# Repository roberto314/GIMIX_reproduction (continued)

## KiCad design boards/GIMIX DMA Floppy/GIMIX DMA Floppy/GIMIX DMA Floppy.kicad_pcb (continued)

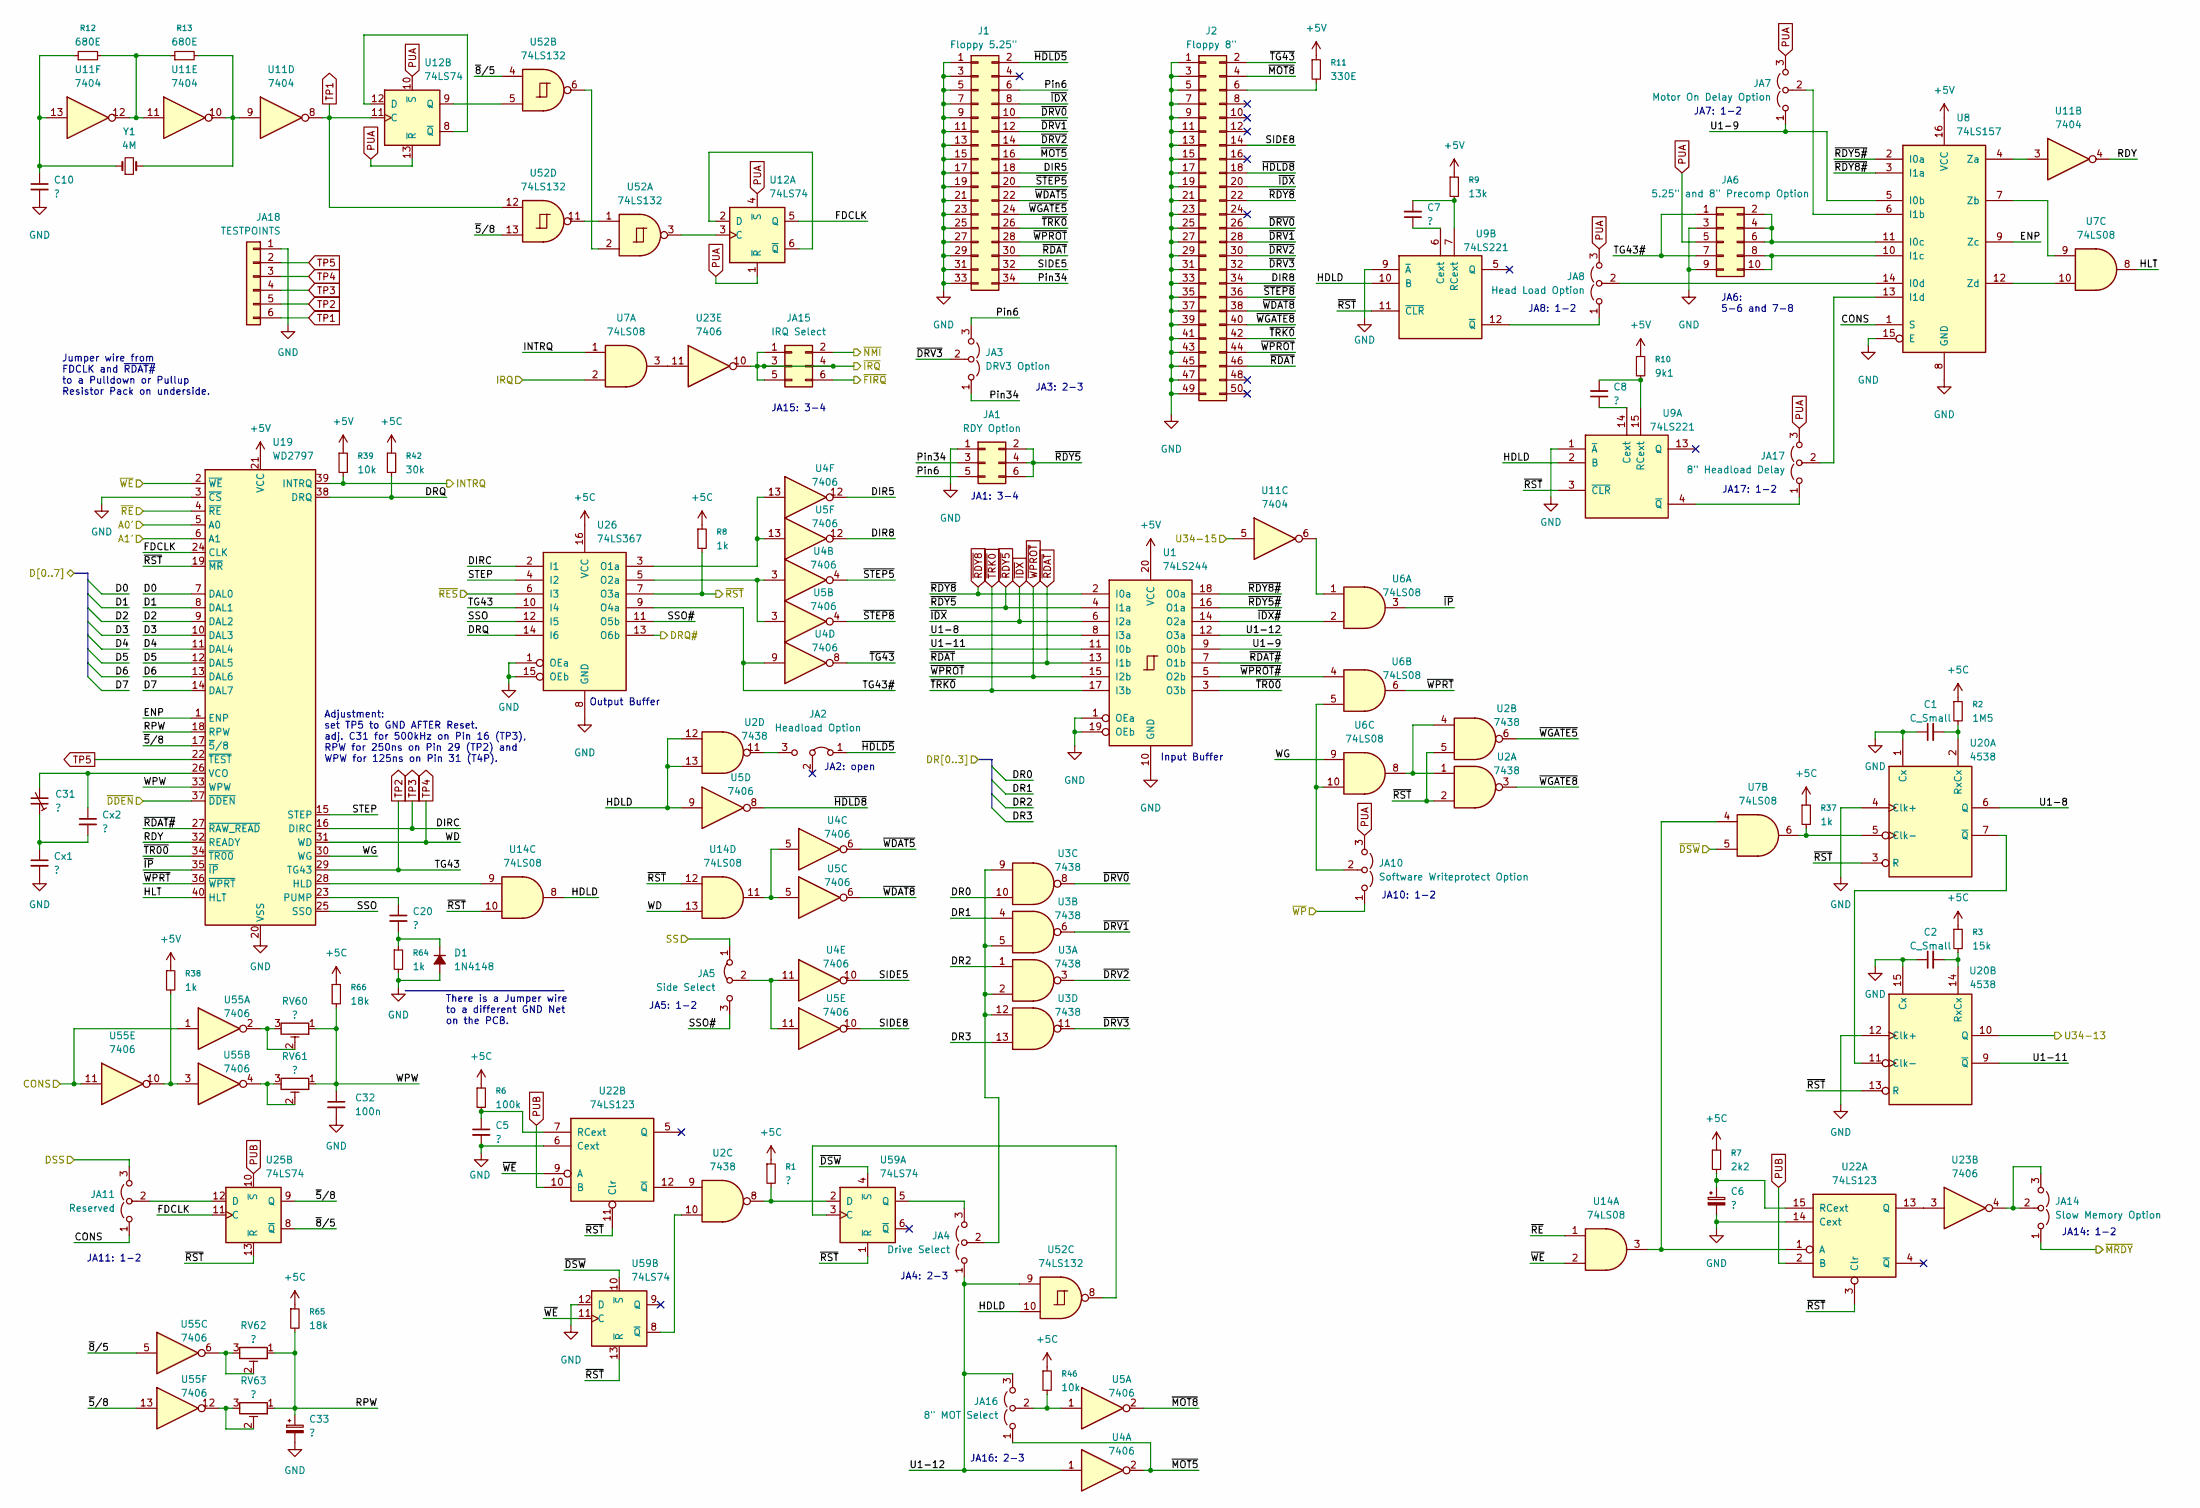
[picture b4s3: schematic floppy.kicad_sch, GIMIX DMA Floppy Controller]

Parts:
C1, C2: C_Small; C_Disc_D3.0mm_W1.6mm_P2.50mm
C5, C7, C8, C33: ?; C_Disc_D3.0mm_W1.6mm_P2.50mm
C6, C10: ?; C_Disc_D4.7mm_W2.5mm_P5.00mm
C20: ?; C_Rect_L11.0mm_W5.1mm_P10.00mm_MKT
C31: ?; Capacitor_Trim
C32: 100n; C_Disc_D3.0mm_W1.6mm_P2.50mm
Cx1, Cx2: ?; C_1206_3216Metric_Pad1.33x1.80mm_HandSolder
D1: 1N4148; D_A-405_P10.16mm_Horizontal
J1: Floppy 5.25"; PinHeader_2x17_P2.54mm_Vertical
J2: Floppy 8"; PinHeader_2x25_P2.54mm_Vertical
JA1: RDY Option; PinHeader_2x03_P2.54mm_Vertical
JA2: Headload Option; PinHeader_1x03_P2.54mm_Vertical
JA3: DRV3 Option; PinHeader_1x03_P2.54mm_Vertical
JA4: Drive Select; PinHeader_1x03_P2.54mm_Vertical
JA5: Side Select; PinHeader_1x03_P2.54mm_Vertical
JA6: 5.25" and 8" Precomp Option; PinHeader_2x05_P2.54mm_Vertical
JA7: Motor On Delay Option; PinHeader_1x03_P2.54mm_Vertical
JA8: Head Load Option; PinHeader_1x03_P2.54mm_Vertical
JA10: Software Writeprotect Option; PinHeader_1x03_P2.54mm_Vertical
JA11: Reserved; PinHeader_1x03_P2.54mm_Vertical
JA14: Slow Memory Option; PinHeader_1x03_P2.54mm_Vertical
JA15: IRQ Select; PinHeader_2x03_P2.54mm_Vertical
JA16: 8" MOT Select; PinHeader_1x03_P2.54mm_Vertical
JA17: 8" Headload Delay; PinHeader_1x03_P2.54mm_Vertical
JA18: TESTPOINTS; PinHeader_1x06_P2.54mm_Vertical
R1: ?; R_Axial_DIN0207_L6.3mm_D2.5mm_P10.16mm_Horizontal
R2: 1M5; R_Axial_DIN0207_L6.3mm_D2.5mm_P10.16mm_Horizontal
R3: 15k; R_Axial_DIN0207_L6.3mm_D2.5mm_P10.16mm_Horizontal
R6: 100k; R_Axial_DIN0207_L6.3mm_D2.5mm_P10.16mm_Horizontal
R7: 2k2; R_Axial_DIN0207_L6.3mm_D2.5mm_P10.16mm_Horizontal
R8, R37, R38, R64: 1k; R_Axial_DIN0207_L6.3mm_D2.5mm_P10.16mm_Horizontal
R9: 13k; R_Axial_DIN0207_L6.3mm_D2.5mm_P10.16mm_Horizontal
R10: 9k1; R_Axial_DIN0207_L6.3mm_D2.5mm_P10.16mm_Horizontal
R11: 330E; R_Axial_DIN0207_L6.3mm_D2.5mm_P10.16mm_Horizontal
R12, R13: 680E; R_Axial_DIN0207_L6.3mm_D2.5mm_P10.16mm_Horizontal
R39, R46: 10k; R_Axial_DIN0207_L6.3mm_D2.5mm_P10.16mm_Horizontal
R42: 30k; R_Axial_DIN0207_L6.3mm_D2.5mm_P10.16mm_Horizontal
R65, R66: 18k; R_Axial_DIN0207_L6.3mm_D2.5mm_P10.16mm_Horizontal
RV60, RV61, RV62, RV63: ?; Potentiometer_Bourns_3005_Horizontal
U1: 74LS244; DIP-20_W7.62mm
U2, U3: 7438; DIP-14_W7.62mm
U4, U5, U23, U55: 7406; DIP-14_W7.62mm
U6, U7, U14: 74LS08; DIP-14_W7.62mm
U8: 74LS157; DIP-16_W7.62mm
U9: 74LS221; DIP-16_W7.62mm
U11: 7404; DIP-14_W7.62mm
U12, U25, U59: 74LS74; DIP-14_W7.62mm
U19: WD2797; DIP-40_W15.24mm
U20: 4538; DIP-16_W7.62mm
U22: 74LS123; DIP-16_W7.62mm
U26: 74LS367; DIP-16_W7.62mm
U52: 74LS132; DIP-14_W7.62mm
Y1: 4M; Crystal_HC49-U_Vertical

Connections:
+5C: R1.1, R2.1, R3.1, R6.1, R7.1, R8.1, R37.1, R42.1, R46.1, R65.1, R66.1, U26.16 (VCC); also elsewhere on the board
+5V: R9.1, R10.1, R11.1, R38.1, R39.1, U1.20 (VCC), U8.16 (VCC), U19.21 (VCC); also elsewhere on the board
/A0': U19.5 (A0); also elsewhere on the board
/A1': U19.6 (A1); also elsewhere on the board
/CONS: JA11.1 (A), U8.1 (S), U55.1, U55.11; also elsewhere on the board
/D0: U19.7 (DAL0); also elsewhere on the board
/D1: U19.8 (DAL1); also elsewhere on the board
/D2: U19.9 (DAL2); also elsewhere on the board
/D3: U19.10 (DAL3); also elsewhere on the board
/D4: U19.11 (DAL4); also elsewhere on the board
/D5: U19.12 (DAL5); also elsewhere on the board
/D6: U19.13 (DAL6); also elsewhere on the board
/D7: U19.14 (DAL7); also elsewhere on the board
/DR0: U3.10; also elsewhere on the board
/DR1: U3.4; also elsewhere on the board
/DR2: U3.1; also elsewhere on the board
/DR3: U3.13; also elsewhere on the board
/DRQ#: U26.13 (O6b); also elsewhere on the board
/DSS: JA11.3 (B); also elsewhere on the board
/Floppy Controller/DIR5: J1.18, U4.12
/Floppy Controller/DIR8: J2.34, U5.12
/Floppy Controller/DRQ: R42.2, U19.38 (DRQ), U26.14 (I6)
/Floppy Controller/ENP: U8.9 (Zc), U19.1 (ENP)
/Floppy Controller/FDCLK: U12.5 (Q), U19.24 (CLK), U25.11 (C)
/Floppy Controller/HDLD: U2.12, U2.13, U5.9, U9.2 (B), U9.10 (B), U14.8, U52.10
/Floppy Controller/HLT: U7.8, U19.40 (HLT)
/Floppy Controller/Pin6: J1.6, JA1.5, JA3.3 (B)
/Floppy Controller/Pin34: J1.34, JA1.3, JA3.1 (A)
/Floppy Controller/RDY: U11.4, U19.32 (READY)
/Floppy Controller/RPW: C33.1, R65.2, RV62.1, RV63.1, U19.18 (RPW)
/Floppy Controller/SIDE5: J1.32, U4.10
/Floppy Controller/SIDE8: J2.14, U5.10
/Floppy Controller/SSO: U19.25 (SSO), U26.12 (I5)
/Floppy Controller/SSO#: JA5.3 (B), U26.11 (O5b)
/Floppy Controller/STEP: U19.15 (STEP), U26.4 (I2)
/Floppy Controller/TG43#: JA6.1, JA6.7, U4.9, U26.9 (O4a)
/Floppy Controller/U1-8: U1.8 (I3a), U20.6 (Q)
/Floppy Controller/U1-9: JA7.1 (A), U1.9 (O0b), U8.5 (I0b)
/Floppy Controller/U1-11: U1.11 (I0b), U20.9 (~Q)
/Floppy Controller/U1-12: JA4.1 (A), JA16.3 (B), U1.12 (O3a), U4.1, U52.9
/Floppy Controller/WG: U6.9, U19.30 (WG)
/Floppy Controller/WPW: C32.1, R66.2, RV60.1, RV61.1, U19.33 (WPW)
/Floppy Controller/~5/8: U19.17 (~5/8), U25.9 (Q), U52.13, U55.13
/Floppy Controller/~8/5: U25.8 (~Q), U52.4, U55.5
/Floppy Controller/~DRV0: J1.10, J2.26, U3.8
/Floppy Controller/~DRV1: J1.12, J2.28, U3.6
/Floppy Controller/~DRV2: J1.14, J2.30, U3.3
/Floppy Controller/~DRV3: J2.32, JA3.2 (C), U3.11
/Floppy Controller/~HDLD5: J1.2, JA2.1 (A)
/Floppy Controller/~HDLD8: J2.18, U5.8
/Floppy Controller/~IDX#: U1.14 (O2a), U6.2
/Floppy Controller/~IP: U6.3, U19.35 (~IP)
/Floppy Controller/~MOT5: J1.16, JA16.1 (A), U4.2
/Floppy Controller/~MOT8: J2.4, U5.2
/Floppy Controller/~RDAT#: U1.7 (O1b), U19.27 (~RAW_READ)
/Floppy Controller/~RDY5#: U1.16 (O1a), U8.2 (I0a)
/Floppy Controller/~RDY8#: U1.18 (O0a), U8.3 (I1a)
/Floppy Controller/~STEP5: J1.20, U4.4
/Floppy Controller/~STEP8: J2.36, U5.4
/Floppy Controller/~TG43: J2.2, U4.8
/Floppy Controller/~TR00: U1.3 (O3b), U19.34 (~TR00)
/Floppy Controller/~WDAT5: J1.22, U4.6
/Floppy Controller/~WDAT8: J2.38, U5.6
/Floppy Controller/~WGATE5: J1.24, U2.6
/Floppy Controller/~WGATE8: J2.40, U2.3
/Floppy Controller/~WPROT#: U1.5 (O2b), U6.4
/Floppy Controller/~WPRT: U6.6, U19.36 (~WPRT)
/INTRQ: R39.2, U7.1, U19.39 (INTRQ); also elsewhere on the board
/IRQ: U7.2; also elsewhere on the board
/SS: JA5.1 (A); also elsewhere on the board
/U34-13: U20.10 (Q); also elsewhere on the board
/U34-15: U11.5; also elsewhere on the board
/~DDEN: U19.37 (~DDEN); also elsewhere on the board
/~DSW: U7.5, U59.4 (~S), U59.10 (~S); also elsewhere on the board
/~FIRQ: JA15.6; also elsewhere on the board
/~IRQ: JA15.1, JA15.3, JA15.4, JA15.5, U23.10; also elsewhere on the board
/~MRDY: JA14.1 (A); also elsewhere on the board
/~NMI: JA15.2; also elsewhere on the board
/~RES: U26.6 (I3); also elsewhere on the board
/~RE: U14.1, U19.4 (~RE); also elsewhere on the board
/~RST: R8.2, U2.2, U2.5, U9.3 (~CLR), U9.11 (~CLR), U14.10, U14.12, U19.19 (~MR), U20.3 (R), U20.13 (R), U22.3 (Clr), U22.11 (Clr), U25.13 (~R), U26.7 (O3a), U59.1 (~R), U59.13 (~R); also elsewhere on the board
/~WE: U14.2, U19.2 (~WE), U22.9 (A), U59.11 (C); also elsewhere on the board
/~WP: JA10.1 (A); also elsewhere on the board
GND: C1.1, C2.1, C5.2, C6.2, C10.2, C31.1, C32.2, C33.2, Cx1.1, Cx1.2, Cx2.2, D1.2 (A), J1.1, J1.3, J1.5, J1.7, J1.9, J1.11, J1.13, J1.15, J1.17, J1.19, J1.21, J1.23, J1.25, J1.27, J1.29, J1.31, J1.33, J2.1, J2.3, J2.5, J2.7, J2.9, J2.11, J2.13, J2.15, J2.17, J2.19, J2.21, J2.23, J2.25, J2.27, J2.29, J2.31, J2.33, J2.35, J2.37, J2.39, J2.41, J2.43, J2.45, J2.47, J2.49, JA1.1, JA6.3, JA6.9, JA18.1, R64.2, U1.1 (OEa), U1.10 (GND), U1.19 (OEb), U8.8 (GND), U8.15 (E), U9.1 (~A), U9.9 (~A), U19.3 (~CS), U19.20 (VSS), U20.1 (Cx), U20.4 (Clk+), U20.12 (Clk+), U20.15 (Cx), U22.6 (Cext), U22.14 (Cext), U26.1 (OEa), U26.8 (GND), U26.15 (OEb), U59.12 (D); also elsewhere on the board
unnamed: C10.1, R12.1, U11.13, Y1.1
unnamed: C20.2, D1.1 (K), R64.1
unnamed: J2.6, R11.2
unnamed: JA2.3 (B), U2.11
unnamed: JA4.3 (B), U59.5 (Q)
unnamed: JA4.2 (C), U3.2, U3.5, U3.9, U3.12
unnamed: JA5.2 (C), U4.11, U5.11
unnamed: JA6.2, JA6.4, JA6.6, U8.11 (I0c)
unnamed: JA6.8, JA6.10, U8.10 (I1c)
unnamed: JA7.2 (C), U8.6 (I1b)
unnamed: JA8.1 (A), U9.12 (~Q)
unnamed: JA8.2 (C), U8.14 (I0d)
unnamed: JA10.2 (C), U6.5, U6.10
unnamed: JA11.2 (C), U25.12 (D)
unnamed: JA14.2 (C), JA14.3 (B), U23.4
unnamed: JA16.2 (C), R46.2, U5.1
unnamed: JA17.1 (A), U9.4 (~Q)
unnamed: JA17.2 (C), U8.13 (I1d)
unnamed: R12.2, R13.1, U11.11, U11.12
unnamed: R13.2, U11.9, U11.10, Y1.2
unnamed: R38.2, U55.3, U55.10
unnamed: RV60.2, RV60.3, U55.2
unnamed: RV61.2, RV61.3, U55.4
unnamed: RV62.2, RV62.3, U55.6
unnamed: RV63.2, RV63.3, U55.12
unnamed: U2.1, U2.4, U6.8
unnamed: U8.4 (Za), U11.3
unnamed: U7.9, U8.7 (Zb)
unnamed: U7.10, U8.12 (Zd)
unnamed: C8.1, U9.14 (Cext)
unnamed: C8.2, R10.2, U9.15 (RCext)
unnamed: C7.1, U9.6 (Cext)
unnamed: C7.2, R9.2, U9.7 (RCext)
unnamed: U6.1, U11.6
unnamed: U12.3 (C), U52.3
unnamed: U12.2 (D), U12.6 (~Q)
unnamed: U12.8 (~Q), U12.12 (D)
unnamed: U12.9 (Q), U52.5
unnamed: U4.5, U5.5, U14.11
unnamed: U14.9, U19.28 (HLD)
unnamed: C20.1, U19.23 (PUMP)
unnamed: C31.2, Cx2.1, U19.26 (VCO)
unnamed: R37.2, U7.6, U20.5 (Clk-)
unnamed: C1.2, R2.2, U20.2 (RxCx)
unnamed: U20.7 (~Q), U20.11 (Clk-)
unnamed: C2.2, R3.2, U20.14 (RxCx)
unnamed: U7.4, U14.3, U22.1 (A)
unnamed: U22.13 (Q), U23.3
unnamed: C6.1, R7.2, U22.15 (RCext)
unnamed: C5.1, R6.2, U22.7 (RCext)
unnamed: U2.9, U22.12 (~Q)
unnamed: U7.3, U23.11
unnamed: U4.13, U5.13, U26.3 (O1a)
unnamed: U4.3, U5.3, U26.5 (O2a)
unnamed: U52.1, U52.11
unnamed: U52.2, U52.6
unnamed: U52.8, U59.3 (C)
unnamed: R1.2, U2.8, U59.2 (D)
unnamed: U2.10, U59.8 (~Q)
PUA: JA6.5, JA7.3 (B), JA8.3 (B), JA10.3 (B), JA17.3 (B), U12.1 (~R), U12.4 (~S), U12.10 (~S), U12.13 (~R); also elsewhere on the board
PUB: U22.2 (B), U22.10 (B), U25.10 (~S); also elsewhere on the board
TP1: JA18.6, U11.8, U12.11 (C), U52.12
TP2: JA18.5, U19.29 (TG43), U26.10 (I4)
TP3: JA18.4, U19.16 (DIRC), U26.2 (I1)
TP4: JA18.3, U14.13, U19.31 (WD)
TP5: JA18.2, U19.22 (~TEST)
~IDX: J1.8, J2.20, U1.6 (I2a); also elsewhere on the board
~RDAT: J1.30, J2.46, U1.13 (I1b); also elsewhere on the board
~RDY5: JA1.2, JA1.4, JA1.6, U1.4 (I1a); also elsewhere on the board
~RDY8: J2.22, U1.2 (I0a); also elsewhere on the board
~TRK0: J1.26, J2.42, U1.17 (I3b); also elsewhere on the board
~WPROT: J1.28, J2.44, U1.15 (I2b); also elsewhere on the board

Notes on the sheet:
JA17: 1-2
JA5: 1-2
JA11: 1-2
JA6: 5-6 and 7-8
JA1: 3-4
Output Buffer
Input Buffer
JA16: 2-3
Adjustment: set TP5 to GND AFTER Reset. adj. C31 for 500kHz on Pin 16 (TP3), RPW for 250ns on Pin 29 (TP2) and WPW for 125ns on Pin 31 (T4P).
JA8: 1-2
There is a Jumper wire to a different GND Net on the PCB.
Jumper wire from FDCLK and ~{RDAT#} to a Pulldown or Pullup Resistor Pack on underside.
JA7: 1-2
JA2: open
JA3: 2-3
JA15: 3-4
JA4: 2-3
JA14: 1-2
JA10: 1-2

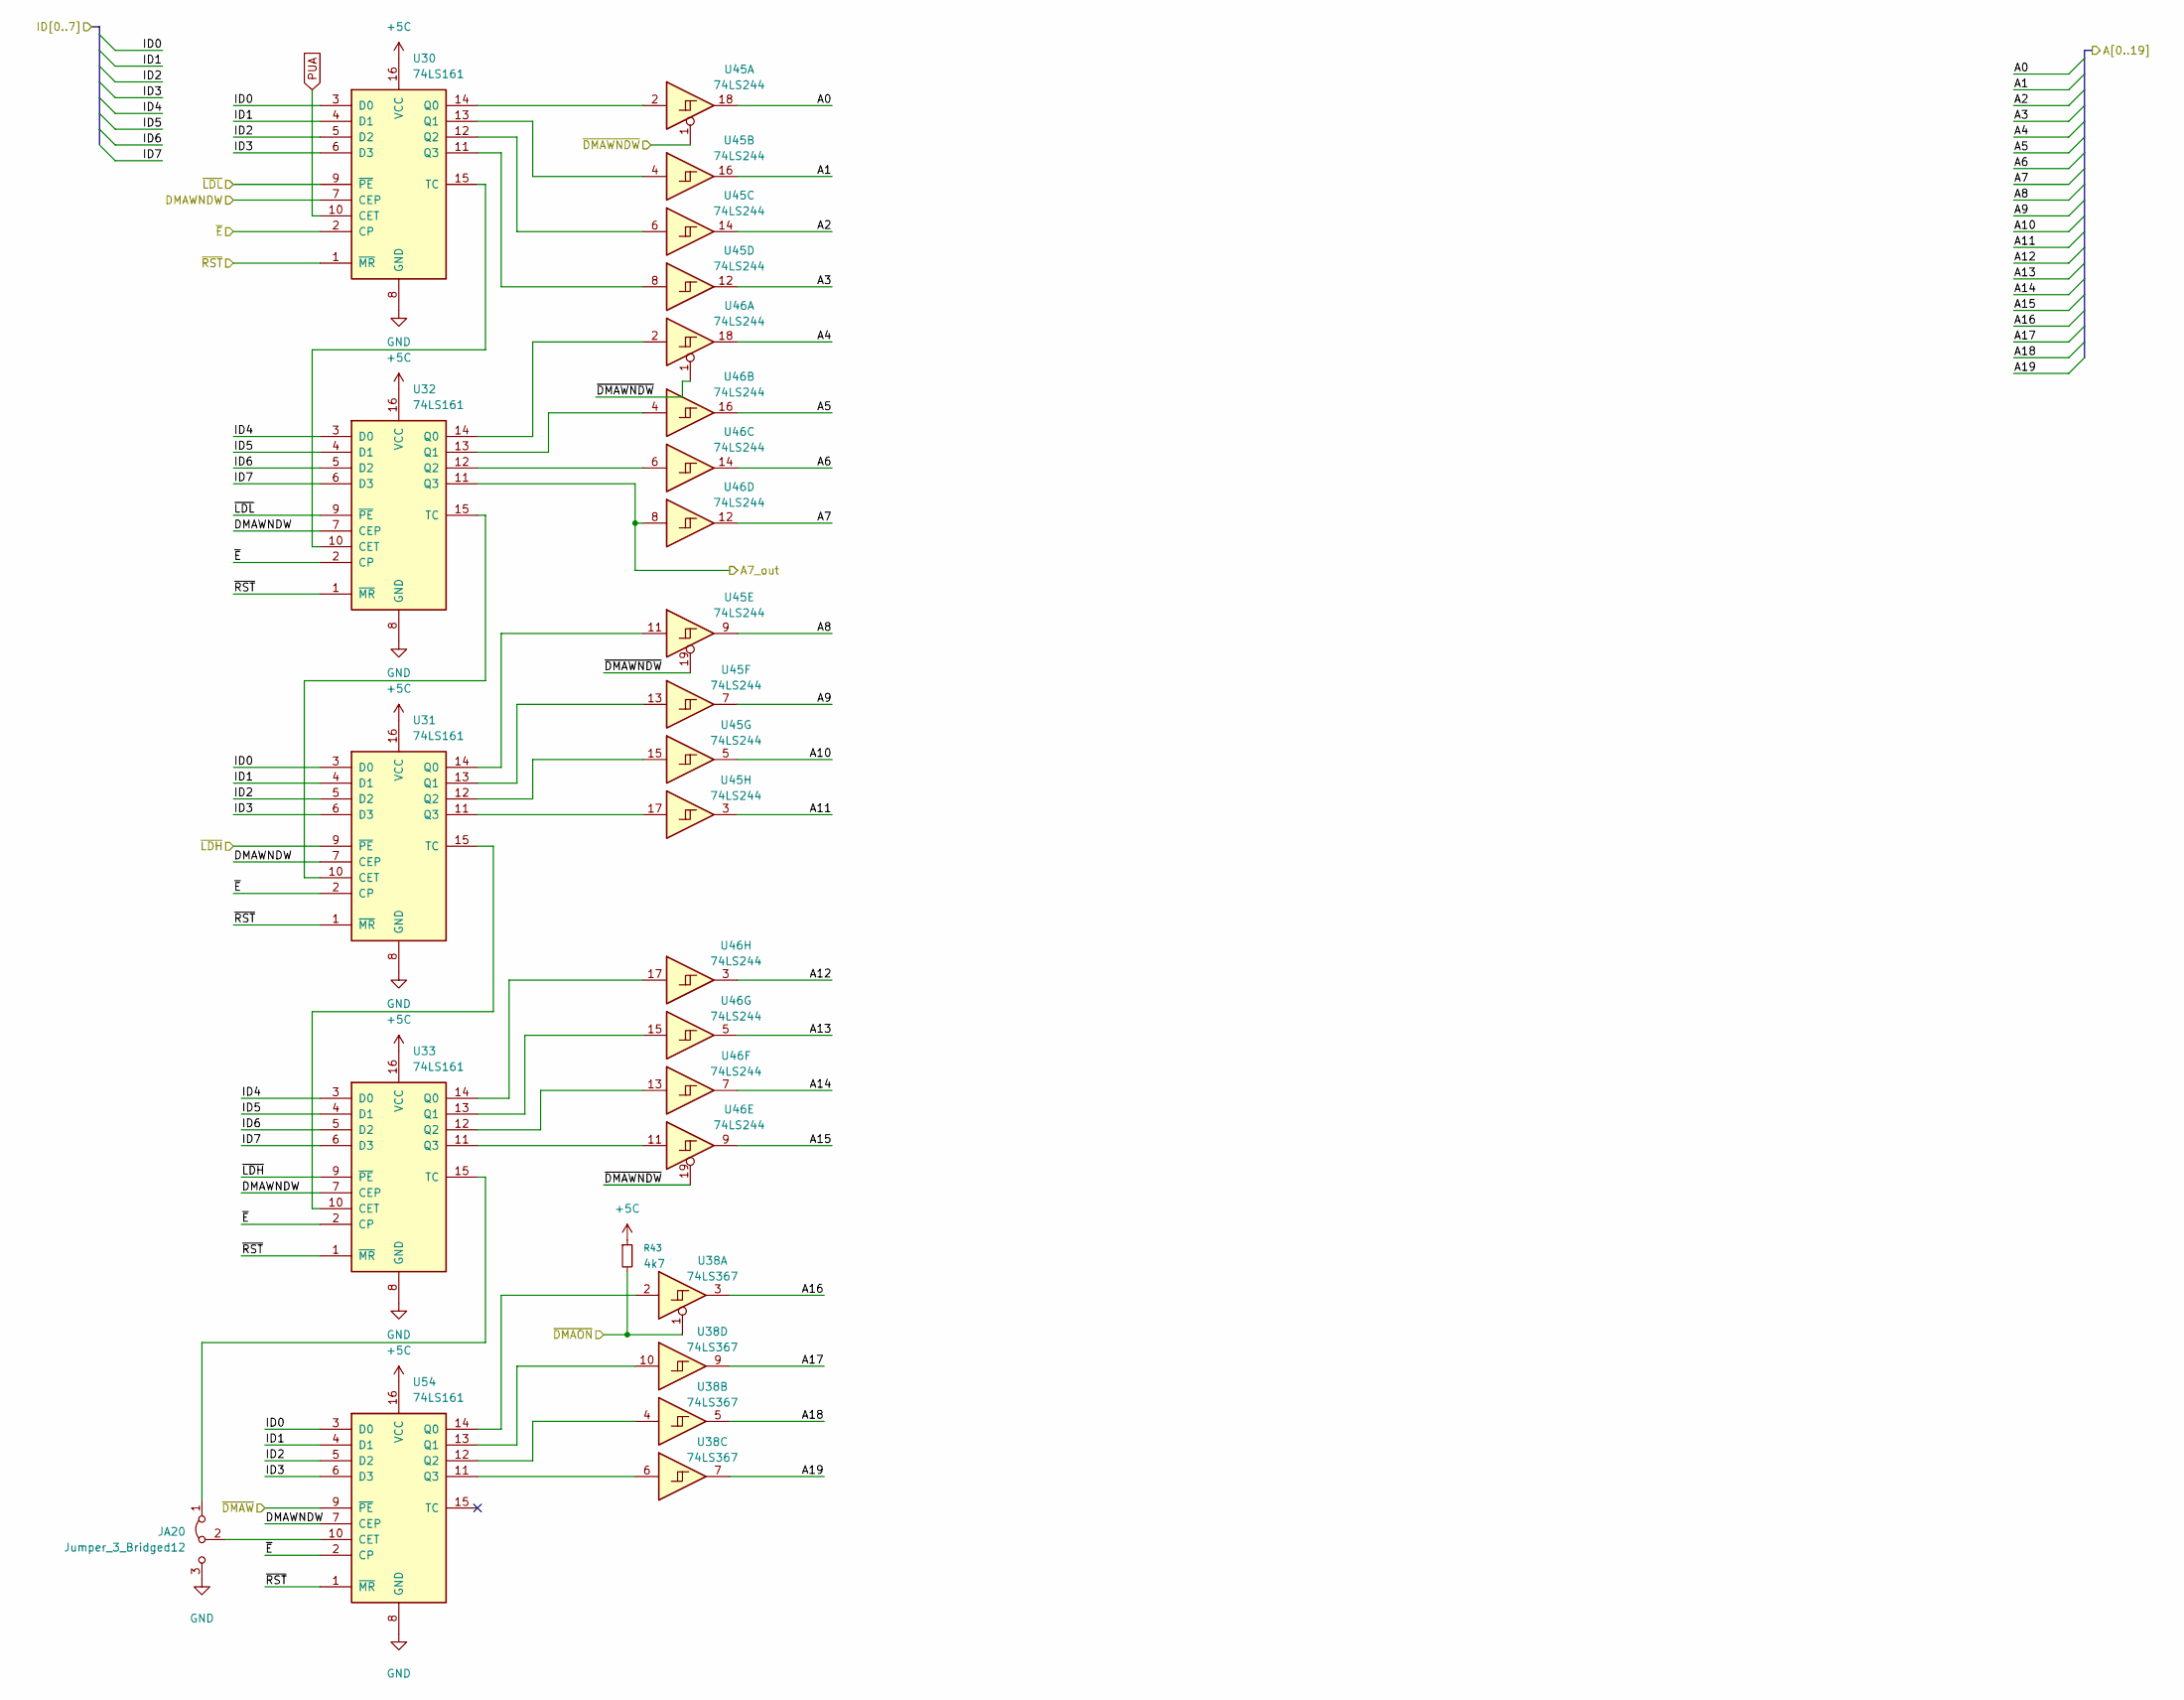
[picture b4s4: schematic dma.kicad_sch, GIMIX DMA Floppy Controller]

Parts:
JA20: Jumper_3_Bridged12; PinHeader_1x03_P2.54mm_Vertical
R43: 4k7; R_Axial_DIN0207_L6.3mm_D2.5mm_P10.16mm_Horizontal
U30, U31, U32, U33, U54: 74LS161; DIP-16_W7.62mm
U38: 74LS367; DIP-16_W7.62mm
U45, U46: 74LS244; DIP-20_W7.62mm

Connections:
+5C: R43.1, U30.16 (VCC), U31.16 (VCC), U32.16 (VCC), U33.16 (VCC), U54.16 (VCC); also elsewhere on the board
/A0: U45.18; also elsewhere on the board
/A1: U45.16; also elsewhere on the board
/A2: U45.14; also elsewhere on the board
/A3: U45.12; also elsewhere on the board
/A4: U46.18; also elsewhere on the board
/A5: U46.16; also elsewhere on the board
/A6: U46.14; also elsewhere on the board
/A7: U46.12; also elsewhere on the board
/A7_out: U32.11 (Q3), U46.8; also elsewhere on the board
/A8: U45.9; also elsewhere on the board
/A9: U45.7; also elsewhere on the board
/A10: U45.5; also elsewhere on the board
/A11: U45.3; also elsewhere on the board
/A12: U46.3; also elsewhere on the board
/A13: U46.5; also elsewhere on the board
/A14: U46.7; also elsewhere on the board
/A15: U46.9; also elsewhere on the board
/A16: U38.3; also elsewhere on the board
/A17: U38.9; also elsewhere on the board
/A18: U38.5; also elsewhere on the board
/A19: U38.7; also elsewhere on the board
/DMAWNDW: U30.7 (CEP), U31.7 (CEP), U32.7 (CEP), U33.7 (CEP), U54.7 (CEP); also elsewhere on the board
/ID0: U30.3 (D0), U31.3 (D0), U54.3 (D0); also elsewhere on the board
/ID1: U30.4 (D1), U31.4 (D1), U54.4 (D1); also elsewhere on the board
/ID2: U30.5 (D2), U31.5 (D2), U54.5 (D2); also elsewhere on the board
/ID3: U30.6 (D3), U31.6 (D3), U54.6 (D3); also elsewhere on the board
/ID4: U32.3 (D0), U33.3 (D0); also elsewhere on the board
/ID5: U32.4 (D1), U33.4 (D1); also elsewhere on the board
/ID6: U32.5 (D2), U33.5 (D2); also elsewhere on the board
/ID7: U32.6 (D3), U33.6 (D3); also elsewhere on the board
/~DMAON: R43.2, U38.1; also elsewhere on the board
/~DMAWNDW: U45.1, U45.19, U46.1, U46.19; also elsewhere on the board
/~DMAW: U54.9 (~PE); also elsewhere on the board
/~E: U30.2 (CP), U31.2 (CP), U32.2 (CP), U33.2 (CP), U54.2 (CP); also elsewhere on the board
/~LDH: U31.9 (~PE), U33.9 (~PE); also elsewhere on the board
/~LDL: U30.9 (~PE), U32.9 (~PE); also elsewhere on the board
/~RST: U30.1 (~MR), U31.1 (~MR), U32.1 (~MR), U33.1 (~MR), U54.1 (~MR); also elsewhere on the board
GND: JA20.3 (B), U30.8 (GND), U31.8 (GND), U32.8 (GND), U33.8 (GND), U54.8 (GND); also elsewhere on the board
unnamed: JA20.1 (A), U33.15 (TC)
unnamed: JA20.2 (C), U54.10 (CET)
unnamed: U30.14 (Q0), U45.2
unnamed: U30.13 (Q1), U45.4
unnamed: U30.12 (Q2), U45.6
unnamed: U30.11 (Q3), U45.8
unnamed: U30.15 (TC), U32.10 (CET)
unnamed: U31.10 (CET), U32.15 (TC)
unnamed: U31.14 (Q0), U45.11
unnamed: U31.13 (Q1), U45.13
unnamed: U31.12 (Q2), U45.15
unnamed: U31.11 (Q3), U45.17
unnamed: U31.15 (TC), U33.10 (CET)
unnamed: U32.14 (Q0), U46.2
unnamed: U32.13 (Q1), U46.4
unnamed: U32.12 (Q2), U46.6
unnamed: U33.14 (Q0), U46.17
unnamed: U33.13 (Q1), U46.15
unnamed: U33.12 (Q2), U46.13
unnamed: U33.11 (Q3), U46.11
unnamed: U38.2, U54.14 (Q0)
unnamed: U38.10, U54.13 (Q1)
unnamed: U38.4, U54.12 (Q2)
unnamed: U38.6, U54.11 (Q3)
PUA: U30.10 (CET); also elsewhere on the board

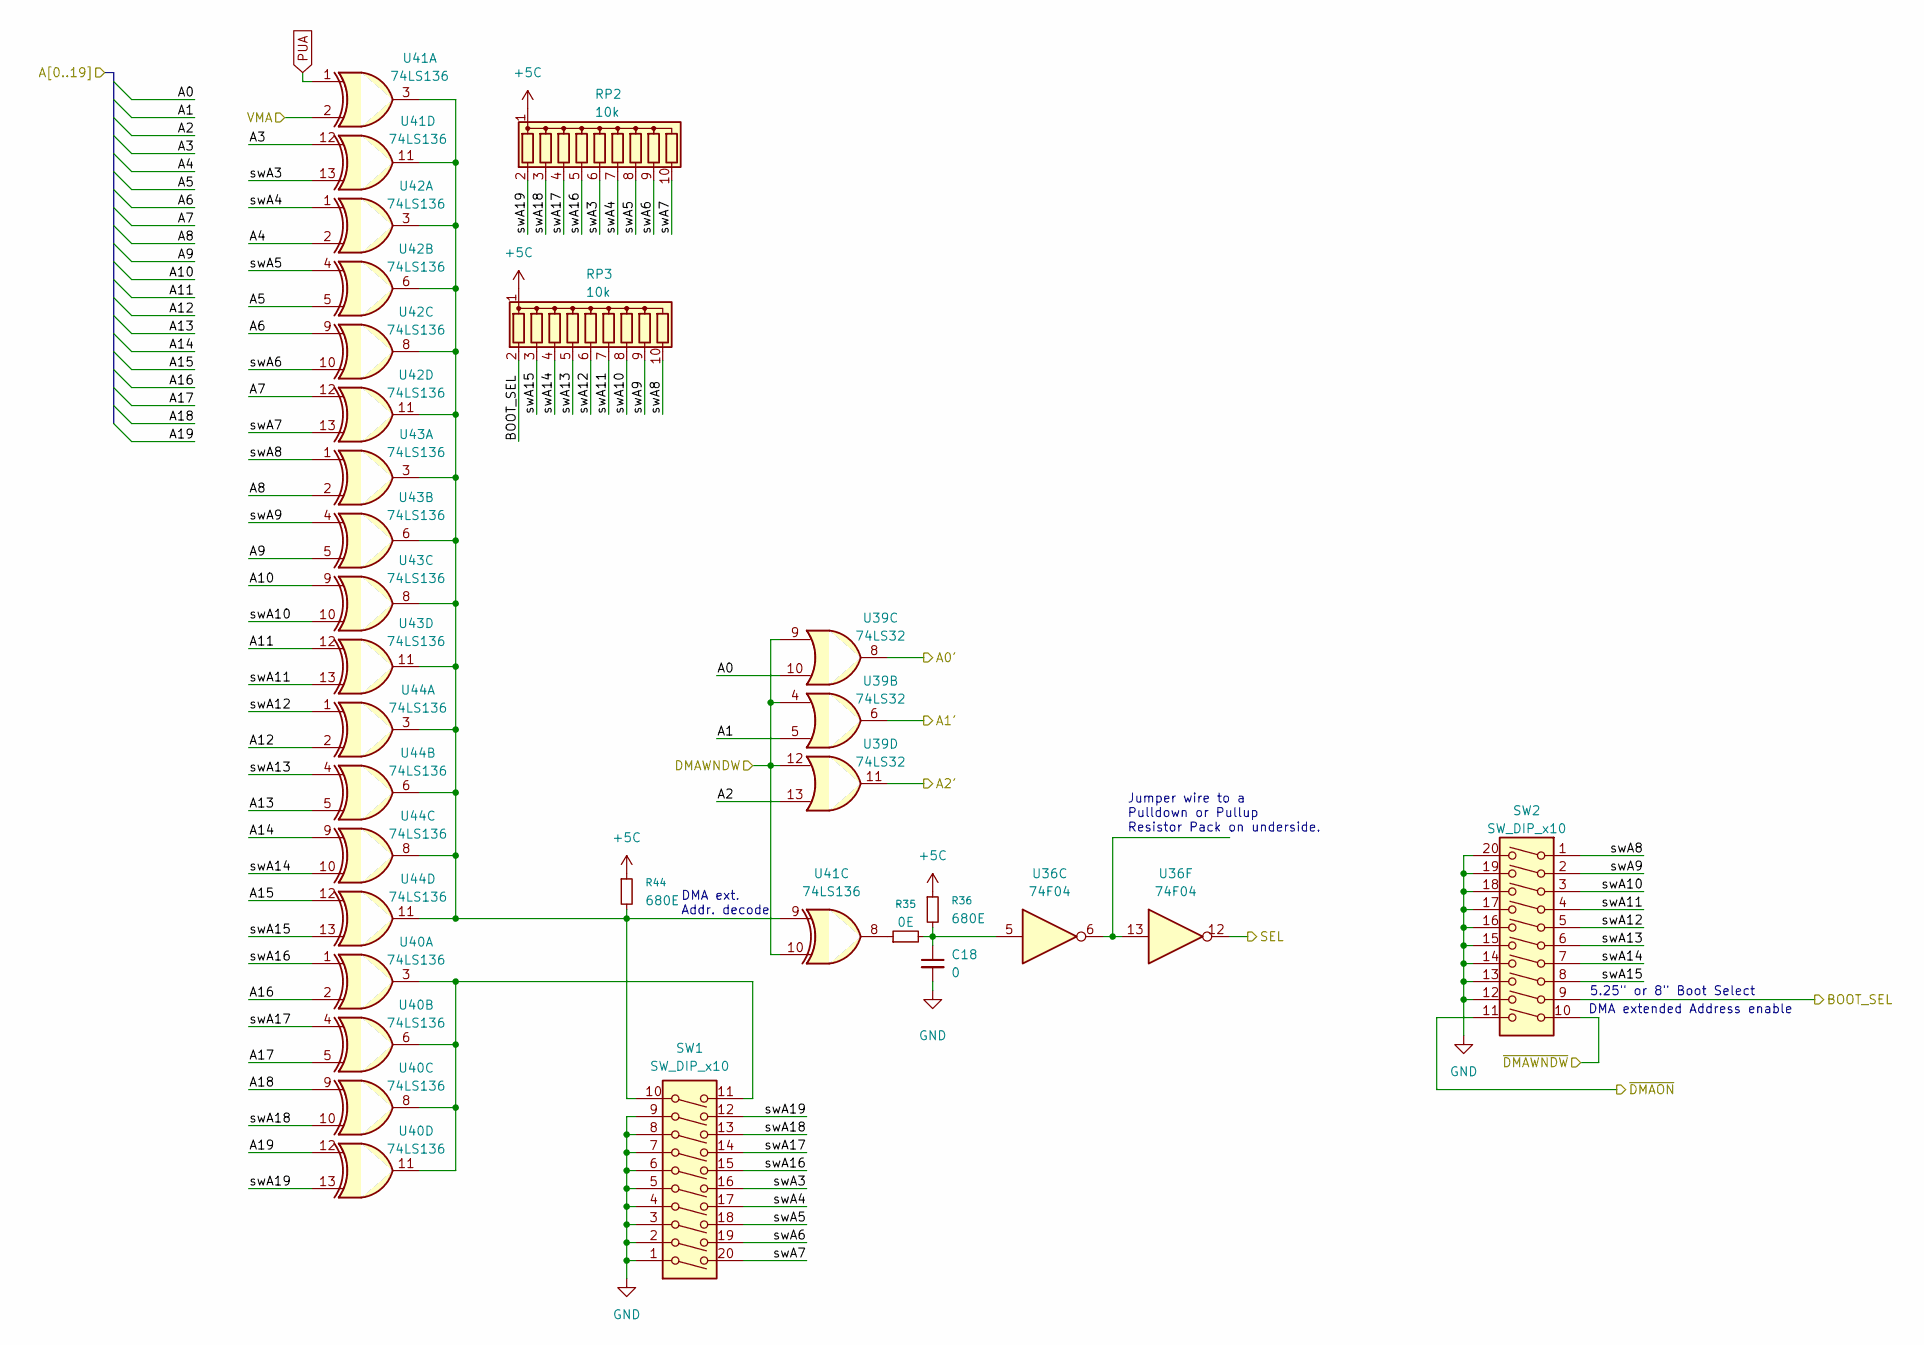
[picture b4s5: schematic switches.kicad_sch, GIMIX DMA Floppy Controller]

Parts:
C18: 0; C_Disc_D4.7mm_W2.5mm_P5.00mm
R35: 0E; R_Axial_DIN0207_L6.3mm_D2.5mm_P10.16mm_Horizontal
R36, R44: 680E; R_Axial_DIN0207_L6.3mm_D2.5mm_P10.16mm_Horizontal
RP2, RP3: 10k; R_Array_SIP10
SW1, SW2: SW_DIP_x10; DIP-20_W7.62mm
U36: 74F04; DIP-14_W7.62mm
U39: 74LS32; DIP-14_W7.62mm
U40, U41, U42, U43, U44: 74LS136; DIP-14_W7.62mm

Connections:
+5C: R36.1, R44.1, RP2.1 (common), RP3.1 (common); also elsewhere on the board
/A0: U39.10; also elsewhere on the board
/A0': U39.8; also elsewhere on the board
/A1: U39.5; also elsewhere on the board
/A1': U39.6; also elsewhere on the board
/A2: U39.13; also elsewhere on the board
/A2': U39.11; also elsewhere on the board
/A3: U41.12; also elsewhere on the board
/A4: U42.2; also elsewhere on the board
/A5: U42.5; also elsewhere on the board
/A6: U42.9; also elsewhere on the board
/A7: U42.12; also elsewhere on the board
/A8: U43.2; also elsewhere on the board
/A9: U43.5; also elsewhere on the board
/A10: U43.9; also elsewhere on the board
/A11: U43.12; also elsewhere on the board
/A12: U44.2; also elsewhere on the board
/A13: U44.5; also elsewhere on the board
/A14: U44.9; also elsewhere on the board
/A15: U44.12; also elsewhere on the board
/A16: U40.2; also elsewhere on the board
/A17: U40.5; also elsewhere on the board
/A18: U40.9; also elsewhere on the board
/A19: U40.12; also elsewhere on the board
/BOOT_SEL: RP3.2 (R1), SW2.9; also elsewhere on the board
/DIP Switches/swA3: RP2.6 (R5), SW1.16, U41.13
/DIP Switches/swA4: RP2.7 (R6), SW1.17, U42.1
/DIP Switches/swA5: RP2.8 (R7), SW1.18, U42.4
/DIP Switches/swA6: RP2.9 (R8), SW1.19, U42.10
/DIP Switches/swA7: RP2.10 (R9), SW1.20, U42.13
/DIP Switches/swA8: RP3.10 (R9), SW2.1, U43.1
/DIP Switches/swA9: RP3.9 (R8), SW2.2, U43.4
/DIP Switches/swA10: RP3.8 (R7), SW2.3, U43.10
/DIP Switches/swA11: RP3.7 (R6), SW2.4, U43.13
/DIP Switches/swA12: RP3.6 (R5), SW2.5, U44.1
/DIP Switches/swA13: RP3.5 (R4), SW2.6, U44.4
/DIP Switches/swA14: RP3.4 (R3), SW2.7, U44.10
/DIP Switches/swA15: RP3.3 (R2), SW2.8, U44.13
/DIP Switches/swA16: RP2.5 (R4), SW1.15, U40.1
/DIP Switches/swA17: RP2.4 (R3), SW1.14, U40.4
/DIP Switches/swA18: RP2.3 (R2), SW1.13, U40.10
/DIP Switches/swA19: RP2.2 (R1), SW1.12, U40.13
/DMAWNDW: U39.4, U39.9, U39.12, U41.10; also elsewhere on the board
/SEL: U36.12; also elsewhere on the board
/VMA: U41.2; also elsewhere on the board
/~DMAON: SW2.11; also elsewhere on the board
/~DMAWNDW: SW2.10; also elsewhere on the board
GND: C18.2, SW1.1, SW1.2, SW1.3, SW1.4, SW1.5, SW1.6, SW1.7, SW1.8, SW1.9, SW2.12, SW2.13, SW2.14, SW2.15, SW2.16, SW2.17, SW2.18, SW2.19, SW2.20; also elsewhere on the board
unnamed: C18.1, R35.2, R36.2, U36.5
unnamed: R35.1, U41.8
unnamed: R44.2, SW1.10, U41.3, U41.9, U41.11, U42.3, U42.6, U42.8, U42.11, U43.3, U43.6, U43.8, U43.11, U44.3, U44.6, U44.8, U44.11
unnamed: SW1.11, U40.3, U40.6, U40.8, U40.11
unnamed: U36.6, U36.13
PUA: U41.1; also elsewhere on the board

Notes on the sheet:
5.25" or 8" Boot Select
DMA extended Address enable
DMA ext. Addr. decode
Jumper wire to a Pulldown or Pullup Resistor Pack on underside.

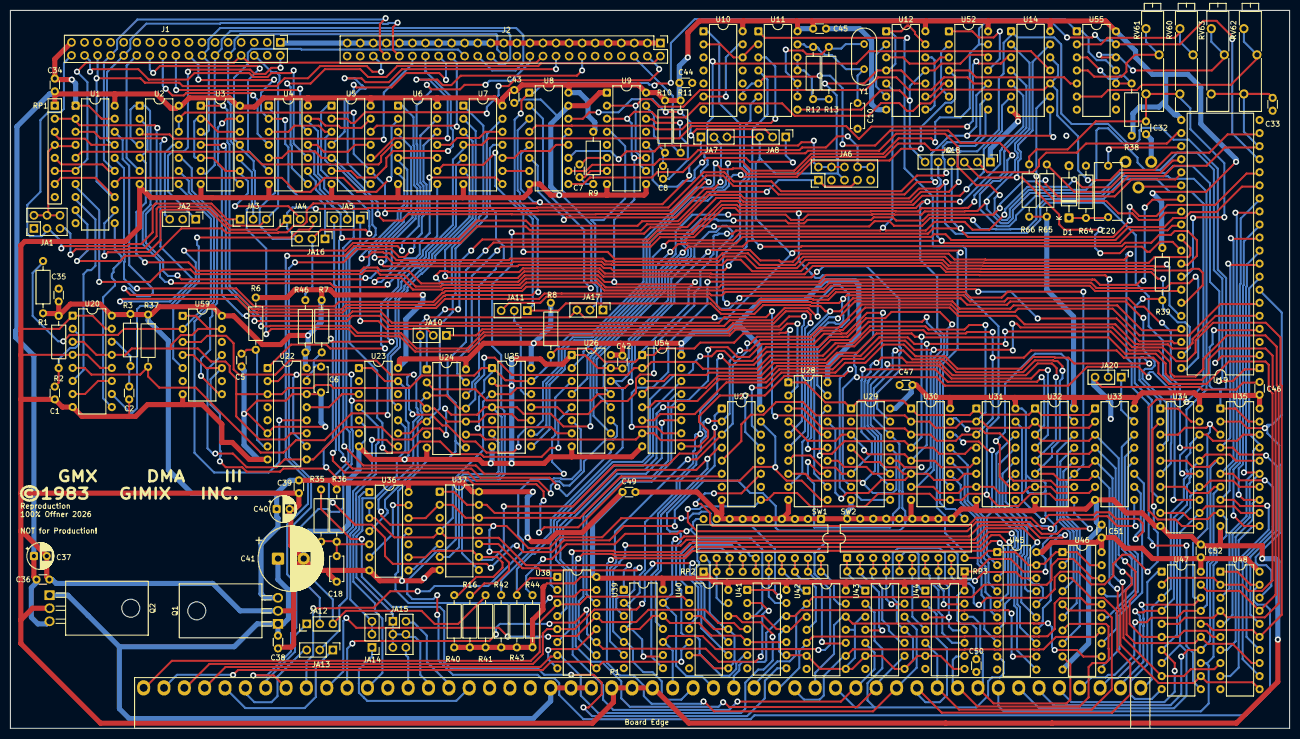
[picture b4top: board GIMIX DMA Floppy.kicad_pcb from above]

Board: 2 copper layers, 248.9 x 139.7 mm, 136 parts (1 on the bottom side), 273 nets.

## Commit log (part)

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2026-06-24 initial
2026-06-24 backup files deleted
2026-06-24 Readme update
2026-06-25 DMS SAS finished
2026-06-25 two port serial board finished finished
2026-06-25 tanner 64k SRAM board finished
2026-06-25 baud rate gen. board finished
2026-06-26 DMA Floppy board finished
2026-06-26 intelligent serial board finished
2026-06-27 both motherboards finished
2026-06-29 new mainboard updated
2026-06-30 DMS SASI ready for production
2026-06-30 Motherboard old version cleanup
